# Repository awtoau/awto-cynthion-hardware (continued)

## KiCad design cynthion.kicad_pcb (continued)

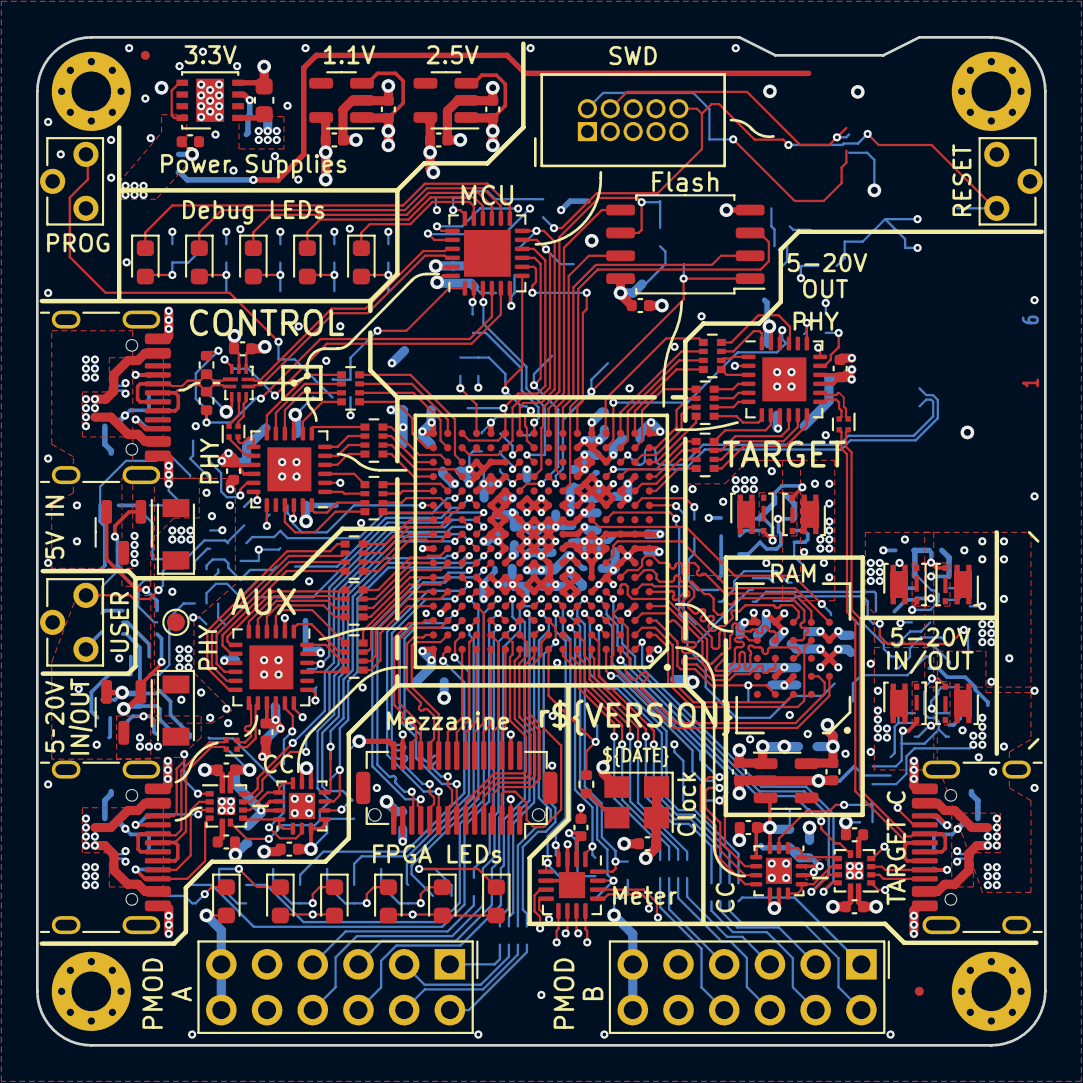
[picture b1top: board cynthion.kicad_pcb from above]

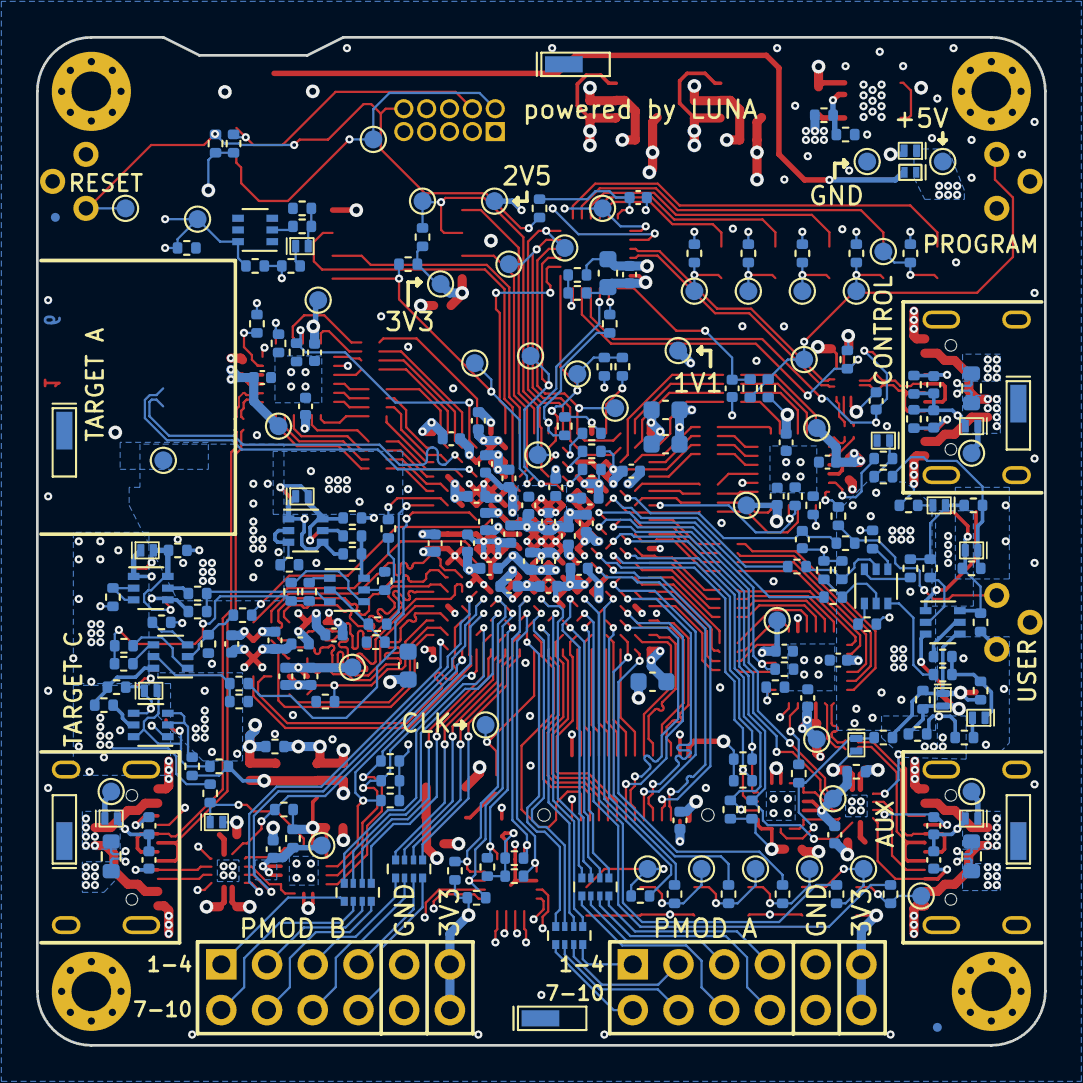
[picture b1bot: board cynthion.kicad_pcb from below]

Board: 6 copper layers, 56.0 x 56.0 mm, 341 parts (249 on the bottom side), 329 nets.

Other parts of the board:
D9: SCHOTTKY; DSN1006-2

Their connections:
+5V: D9.1 (K); also elsewhere on the board
